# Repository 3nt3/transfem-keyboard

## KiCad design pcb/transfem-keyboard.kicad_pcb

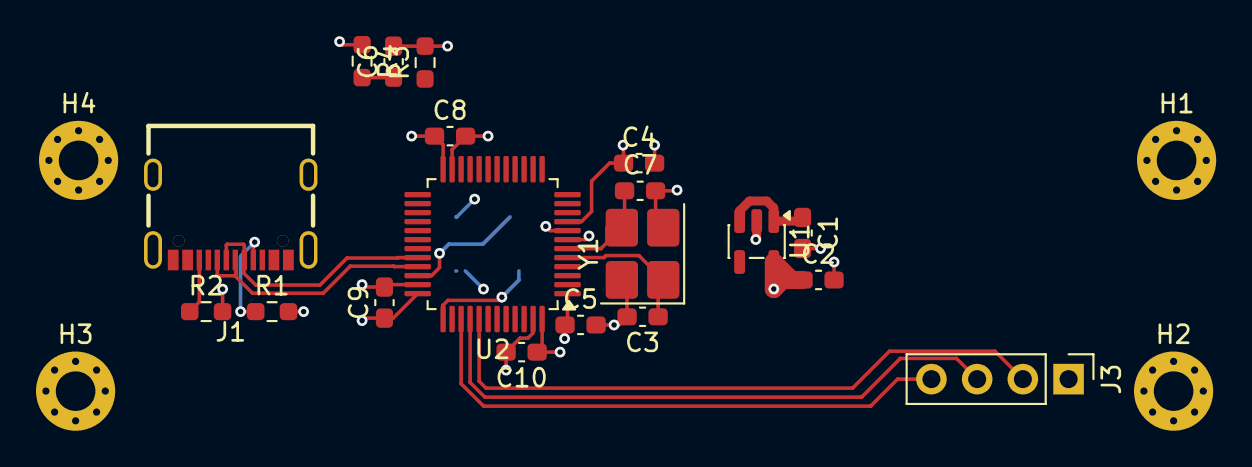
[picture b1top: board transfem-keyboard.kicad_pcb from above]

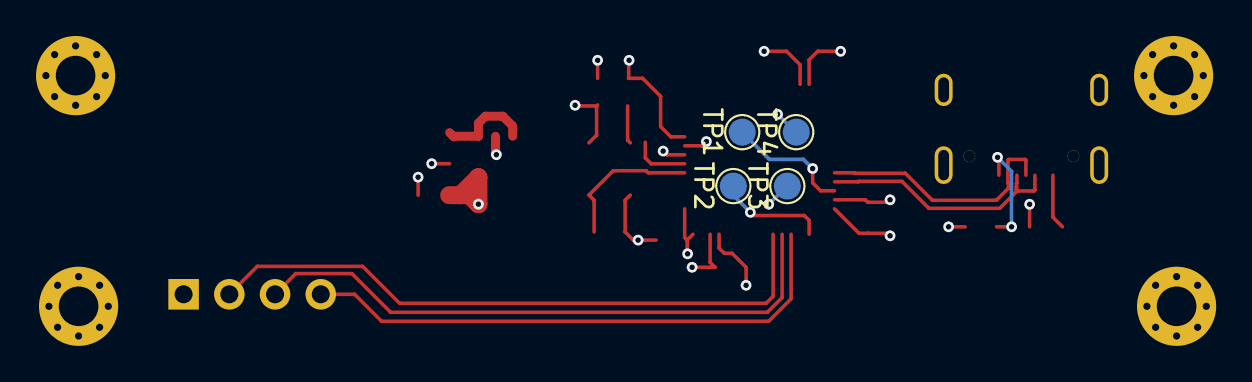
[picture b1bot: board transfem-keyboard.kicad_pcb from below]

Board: 4 copper layers, 27 parts (4 on the bottom side), 16 nets.

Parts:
C1, C2: 1u; C_0603_1608Metric_Pad1.08x0.95mm_HandSolder
C3, C7: 10p; C_0603_1608Metric_Pad1.08x0.95mm_HandSolder
C4, C5, C6, C8, C9, C10: 100n; C_0603_1608Metric_Pad1.08x0.95mm_HandSolder
H1, H2, H3, H4: MountingHole_Pad; MountingHole_2.2mm_M2_Pad_Via
J1: USB_C_Receptacle; USB-C-SMD_MC-311D
J3: Conn_01x04; PinHeader_1x04_P2.54mm_Vertical
R1, R2: 5k1; R_0603_1608Metric_Pad0.98x0.95mm_HandSolder
R3, R4: 10k; R_0603_1608Metric_Pad0.98x0.95mm_HandSolder
TP1, TP2, TP3, TP4: TestPoint; TestPoint_Pad_D1.5mm
U1: LP5907MFX-3.3; SOT-23-5
U2: STM32F103C8Tx; LQFP-48_7x7mm_P0.5mm
Y1: 16MHz; Crystal_SMD_3225-4Pin_3.2x2.5mm_HandSoldering

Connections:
+3V3: C2.1, C4.1, C5.1, C8.1, C9.1, C10.1, R4.1, TP3.1, U1.5 (OUT), U2.1 (VBAT), U2.9 (VDDA), U2.24 (VDD), U2.36 (VDD), U2.48 (VDD)
/BOOT0: R3.1, U2.44 (BOOT0)
/CRYSTAL_1: C3.1, U2.5 (PD0), Y1.1
/CRYSTAL_3: C7.1, U2.6 (PD1), Y1.3
/NRST: C6.1, R4.2, U2.7 (NRST)
/SWCLK: TP2.1, U2.37 (PA14)
/SWDIO: TP1.1, U2.34 (PA13)
/SW_COLON: J3.3, U2.40 (PB4)
/SW_SHIFT: J3.4, U2.39 (PB3)
/SW_THREE: J3.2, U2.41 (PB5)
/USB_D+: J1.A6 (D+), J1.B6 (D+), U2.33 (PA12)
/USB_D-: J1.A7 (D-), J1.B7 (D-), U2.32 (PA11)
GND: C1.2, C2.2, C3.2, C4.2, C5.2, C6.2, C7.2, C8.2, C9.2, C10.2, H1.1, H2.1, H3.1, H4.1, J3.1, R1.2, R2.2, R3.2, TP4.1, U1.2 (GND), U2.8 (VSSA), U2.23 (VSS), U2.35 (VSS), U2.47 (VSS), Y1.2, Y1.4
unnamed: J1.A5 (CC1), R1.1
unnamed: J1.B5 (CC2), R2.1
VBUS: C1.1, U1.1 (IN), U1.3 (EN)

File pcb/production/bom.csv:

Designator,Footprint,Quantity,Value,LCSC Part #
"C1, C2",0603,2,1u,
"C10, C4, C5, C6, C8, C9",0603,6,100n,
"C3, C7",0603,2,10p,
J1,USB-C-SMD_MC-311D,1,USB_C_Receptacle,
J2,JST_SH_SM03B-SRSS-TB_1x03-1MP_P1.00mm_Horizontal,1,Conn_01x03_Socket,
J3,JST_SH_SM04B-SRSS-TB_1x04-1MP_P1.00mm_Horizontal,1,Conn_01x04_Socket,
"R1, R2",0603,2,5k1,
"R3, R4",0603,2,10k,
SW1,SW-SMD_4P-L5.1-W5.1-P3.70-LS6.5-TL_H1.5,1,SW_Push,
U1,SOT-23-5,1,LP5907MFX-3.3,
U2,LQFP-48_7x7mm_P0.5mm,1,STM32F103C8Tx,
Y1,Crystal_SMD_3225-4Pin_3.2x2.5mm_HandSoldering,1,16MHz,

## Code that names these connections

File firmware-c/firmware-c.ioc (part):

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Mcu.Name=STM32F103C(8-B)Tx
Mcu.Package=LQFP48
Mcu.UserName=STM32F103C8Tx
PA11.Mode=Device
PA11.Signal=USB_DM
PA12.Mode=Device
PA12.Signal=USB_DP
PA13.Mode=Serial_Wire
PA13.Signal=SYS_JTMS-SWDIO
PA14.Mode=Serial_Wire
PA14.Signal=SYS_JTCK-SWCLK
PD0-OSC_IN.Mode=HSE-External-Oscillator
PD0-OSC_IN.Signal=RCC_OSC_IN
PD1-OSC_OUT.Mode=HSE-External-Oscillator
PD1-OSC_OUT.Signal=RCC_OSC_OUT
RCC.SYSCLKFreq_VALUE=72000000
RCC.SYSCLKSource=RCC_SYSCLKSOURCE_PLLCLK
board=custom

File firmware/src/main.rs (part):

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        // Pull the D+ pin down to send a RESET condition to the USB bus.
        // This forced reset is needed only for development, without it host
        // will not reset your device when you upload new firmware.
        let _dp = Output::new(p.PA12.reborrow(), Level::High, Speed::Low);
        Timer::after_millis(10).await;
    }

    info!("Hello, World!");

    let driver = Driver::new(p.USB, Irqs, p.PA12, p.PA11);

    // Create embassy-usb config
    let mut config = embassy_usb::Config::new(0xc0de, 0xcafe);
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    let (reader, mut writer) = hid.split();

    // BUTTON GPIOs
    let mut shift_btn = ExtiInput::new(p.PB3, p.EXTI3, Pull::Up);
    let mut colon_btn = ExtiInput::new(p.PB4, p.EXTI4, Pull::Up);
    let mut three_btn = ExtiInput::new(p.PB5, p.EXTI5, Pull::Up);

    let buttons = [
        ButtonConfig {
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
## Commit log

2025-12-09 hello world
2025-12-11 it builds
2025-12-12 idk it just halts after boot
2026-01-08 add c firmware that actually works
2026-01-08 IT WORKS WHOOOO
2026-01-08 add send_text
